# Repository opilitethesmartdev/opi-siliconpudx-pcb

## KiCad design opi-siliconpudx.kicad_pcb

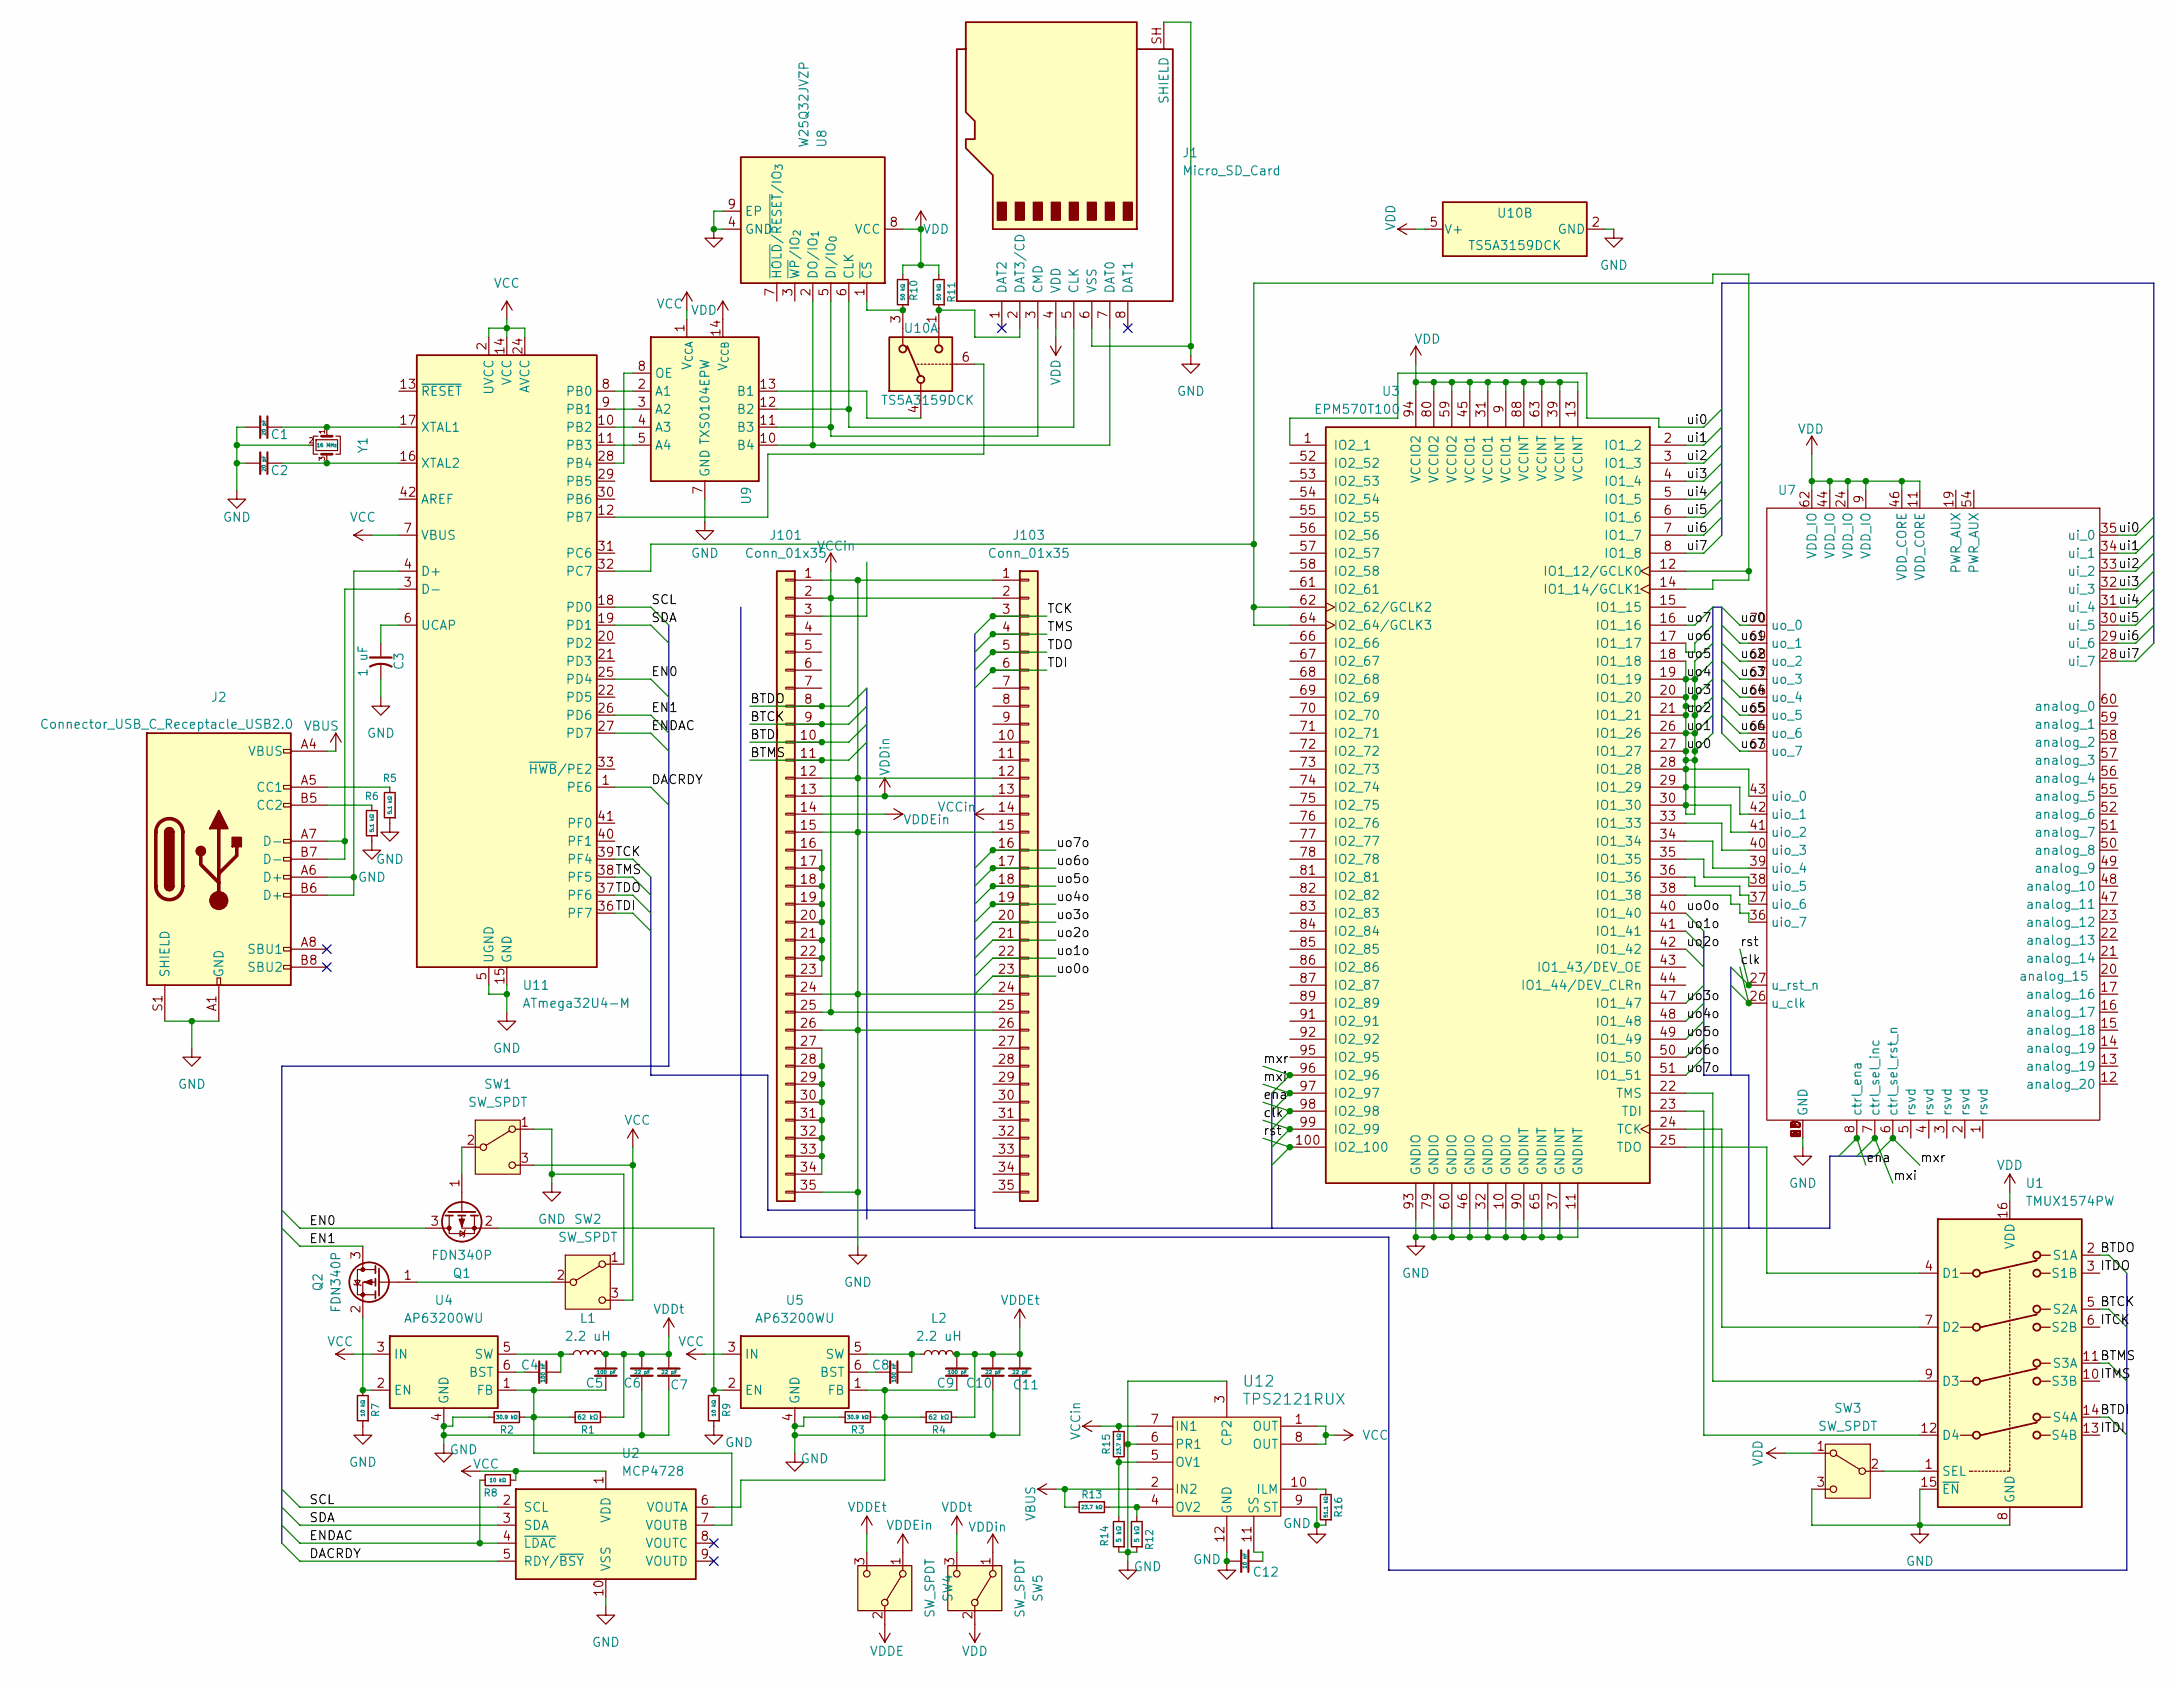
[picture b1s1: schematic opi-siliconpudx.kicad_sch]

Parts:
C1, C2: 20 pF; C_01005_0402Metric
C3: 1 uF; C_0201_0603Metric
C4, C8: 100 nF; C_01005_0402Metric
C5, C9: 100 pF; C_01005_0402Metric
C6, C7, C10, C11: 22 pF; C_01005_0402Metric
C12: 10 nF; C_01005_0402Metric
J1: Micro_SD_Card; microSD_HC_Molex_47219-2001
J2: Connector_USB_C_Receptacle_USB2.0; TYPE-C-31-M-14
J101, J103: Conn_01x35; PinHeader_1x35_P2.54mm_Vertical
L1, L2: 2.2 uH; L_Cenker_CKCS201610
Q1, Q2: FDN340P; SOT-23
R1, R4: 62 kΩ; R_01005_0402Metric
R2, R3: 30.9 kΩ; R_01005_0402Metric
R5, R6: 5.1 kΩ; R_01005_0402Metric
R7, R8, R9: 10 kΩ; R_01005_0402Metric
R10, R11: 50 kΩ; R_01005_0402Metric
R12, R14: 5 kΩ; R_01005_0402Metric
R13, R15: 23.7 kΩ; R_01005_0402Metric
R16: 51.1 kΩ; R_01005_0402Metric
SW1, SW2, SW3, SW4, SW5: SW_SPDT; PinHeader_1x03_P2.00mm_Vertical
U1: TMUX1574PW; TSSOP-16_4.4x5mm_P0.65mm
U2: MCP4728; MSOP-10_3x3mm_P0.5mm
U3: EPM570T100; LQFP-100_14x14mm_P0.5mm
U4, U5: AP63200WU; TSOT-23-6
U7: CONN-SMD_70P-P0.40_HCTL_HC-PBB40C-70DP-0.4V-02
U8: W25Q32JVZP; WSON-8-1EP_6x5mm_P1.27mm_EP3.4x4.3mm
U9: TXS0104EPW; TSSOP-14_4.4x5mm_P0.65mm
U10: TS5A3159DCK; SOT-363_SC-70-6
U11: ATmega32U4-M; QFN-44-1EP_7x7mm_P0.5mm_EP5.2x5.2mm
U12: TPS2121RUX; RUX0012A
Y1: 16 MHz; Crystal_SMD_2016-4Pin_2.0x1.6mm

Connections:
/BTCK: J101.9, U1.5 (S2A)
/BTDI: J101.10, U1.14 (S4A)
/BTDO: J101.8, U1.2 (S1A)
/BTMS: J101.11, U1.11 (S3A)
/DACRDY: U2.5 (RDY/~BSY), U11.1 (PE6)
/EN0: Q1.3 (D), U11.25 (PD4)
/EN1: Q2.3 (D), U11.26 (PD6)
/ENDAC: R8.2, U2.4 (~LDAC), U11.27 (PD7)
/ITCK: U1.6 (S2B)
/ITDI: U1.13 (S4B)
/ITDO: U1.3 (S1B)
/ITMS: U1.10 (S3B)
/SCL: U2.2 (SCL), U11.18 (PD0)
/SDA: U2.3 (SDA), U11.19 (PD1)
/TCK: J103.3, U11.39 (PF4)
/TDI: J103.6, U11.36 (PF7)
/TDO: J103.5, U11.37 (PF6)
/TMS: J103.4, U11.38 (PF5)
/clk: U3.99 (IO2_99), U7.26 (u_clk)
/ena: U3.98 (IO2_98), U7.8 (ctrl_ena)
/mxi: U3.97 (IO2_97), U7.7 (ctrl_sel_inc)
/mxr: U3.96 (IO2_96), U7.6 (ctrl_sel_rst_n)
/rst: U3.100 (IO2_100), U7.27 (u_rst_n)
/ui0: U3.1 (IO2_1), U7.35 (ui_0)
/ui1: U3.2 (IO1_2), U7.34 (ui_1)
/ui2: U3.3 (IO1_3), U7.33 (ui_2)
/ui3: U3.4 (IO1_4), U7.32 (ui_3)
/ui4: U3.5 (IO1_5), U7.31 (ui_4)
/ui5: U3.6 (IO1_6), U7.30 (ui_5)
/ui6: U3.7 (IO1_7), U7.29 (ui_6)
/ui7: U3.8 (IO1_8), U7.28 (ui_7)
/uo0: U3.18 (IO1_18), U3.19 (IO1_19), U3.20 (IO1_20), U3.21 (IO1_21), U3.26 (IO1_26), U3.27 (IO1_27), U3.28 (IO1_28), U3.29 (IO1_29), U3.30 (IO1_30), U7.41 (uio_2), U7.42 (uio_1), U7.43 (uio_0), U7.65 (uo_5), U7.66 (uo_4), U7.67 (uo_3), U7.68 (uo_2), U7.69 (uo_1), U7.70 (uo_0)
/uo0o: J103.23, U3.40 (IO1_40)
/uo1o: J103.22, U3.41 (IO1_41)
/uo2o: J103.21, U3.42 (IO1_42)
/uo3o: J103.20, U3.47 (IO1_47)
/uo4o: J103.19, U3.48 (IO1_48)
/uo5o: J103.18, U3.49 (IO1_49)
/uo6: U3.17 (IO1_17), U7.64 (uo_6)
/uo6o: J103.17, U3.50 (IO1_50)
/uo7: U3.16 (IO1_16), U7.63 (uo_7)
/uo7o: J103.16, U3.51 (IO1_51)
GND: C1.1, C2.1, C3.2, C6.1, C7.1, C10.1, C11.1, C12.2, J1.6 (VSS), J1.SH (SHIELD), J2.A1 (GND), J2.A12 (GND), J2.B1 (GND), J2.B12 (GND), J2.S1 (SHIELD), J101.1, J101.12, J101.15, J101.24, J101.26, J101.35, J103.1, J103.12, J103.15, J103.24, J103.26, R2.1, R3.1, R5.1, R6.1, R7.1, R9.1, R12.1, R14.1, R16.1, SW1.1 (A), SW2.1 (A), SW3.3 (C), U1.8 (GND), U1.15 (~EN), U2.10 (VSS), U3.10 (GNDIO), U3.11 (GNDINT), U3.32 (GNDIO), U3.37 (GNDINT), U3.46 (GNDIO), U3.60 (GNDIO), U3.65 (GNDINT), U3.79 (GNDIO), U3.90 (GNDINT), U3.93 (GNDIO), U4.4 (GND), U5.4 (GND), U7.10 (GND), U7.18 (GND), U7.25 (GND), U7.45 (GND), U7.53 (GND), U7.61 (GND), U7.MP (GND), U8.4 (GND), U8.9 (EP), U9.7 (GND), U10.2 (GND), U11.5 (UGND), U11.15 (GND), U11.23 (GND), U11.35 (GND), U11.43 (GND), U11.45 (GND), U12.3 (CP2), U12.6 (PR1), U12.9 (ST), U12.12 (GND), Y1.2 (G), Y1.4 (G)
unnamed: J1.5 (CLK), U8.6 (CLK), U9.12 (B2)
unnamed: J1.3 (CMD), U8.5 (DI/IO_{0}), U9.11 (B3)
unnamed: J1.7 (DAT0), U8.2 (DO/IO_{1}), U9.10 (B4)
unnamed: J1.2 (DAT3/CD), R11.1, U10.1
unnamed: J2.A5 (CC1), R5.2
unnamed: J2.B5 (CC2), R6.2
unnamed: J101.16, J101.17, J101.18, J101.19, J101.20, J101.21, J101.22, J101.23
unnamed: J101.27, J101.28, J101.29, J101.30, J101.31, J101.32, J101.33, J101.34
unnamed: Q1.1 (G), SW1.2 (B)
unnamed: Q1.2 (S), R9.2, U5.2 (EN)
unnamed: Q2.1 (G), SW2.2 (B)
unnamed: Q2.2 (S), R7.2, U4.2 (EN)
unnamed: SW3.2 (B), U1.1 (SEL)
unnamed: U1.4 (D1), U3.25 (TDO)
unnamed: U1.7 (D2), U3.24 (TCK)
unnamed: U1.9 (D3), U3.22 (TMS)
unnamed: U1.12 (D4), U3.23 (TDI)
unnamed: C9.1, R3.2, R4.1, U2.6 (VOUTA), U5.1 (FB)
unnamed: C5.1, R1.1, R2.2, U2.7 (VOUTB), U4.1 (FB)
unnamed: U3.33 (IO1_33), U7.40 (uio_3)
unnamed: U3.34 (IO1_34), U7.39 (uio_4)
unnamed: U3.35 (IO1_35), U7.38 (uio_5)
unnamed: U3.36 (IO1_36), U7.37 (uio_6)
unnamed: U3.38 (IO1_38), U7.36 (uio_7)
unnamed: C4.1, U4.6 (BST)
unnamed: C4.2, L1.1, U4.5 (SW)
unnamed: C8.1, U5.6 (BST)
unnamed: C8.2, L2.1, U5.5 (SW)
unnamed: R10.1, U8.1 (~CS), U10.3
unnamed: U9.13 (B1), U10.4
unnamed: J2.A6 (D+), J2.B6 (D+), U11.4 (D+)
unnamed: J2.A7 (D-), J2.B7 (D-), U11.3 (D-)
unnamed: U9.2 (A1), U11.8 (PB0)
unnamed: U9.3 (A2), U11.9 (PB1)
unnamed: U9.4 (A3), U11.10 (PB2)
unnamed: U9.5 (A4), U11.11 (PB3)
unnamed: U9.8 (OE), U11.28 (PB4)
unnamed: U10.6, U11.12 (PB7)
unnamed: U3.12 (IO1_12/GCLK0), U3.14 (IO1_14/GCLK1), U3.62 (IO2_62/GCLK2), U3.64 (IO2_64/GCLK3), U11.32 (PC7)
unnamed: C3.1, U11.6 (UCAP)
unnamed: C1.2, U11.17 (XTAL1), Y1.1
unnamed: C2.2, U11.16 (XTAL2), Y1.3
unnamed: R16.2, U12.10 (ILM)
unnamed: R14.2, R15.2, U12.5 (OV1)
unnamed: R12.2, R13.1, U12.4 (OV2)
unnamed: C12.1, U12.11 (SS)
VBUS: J2.A4 (VBUS), J2.A9 (VBUS), J2.B4 (VBUS), J2.B9 (VBUS), R13.2, U12.2 (IN2)
VCC: R8.1, SW1.3 (C), SW2.3 (C), U2.1 (VDD), U4.3 (IN), U5.3 (IN), U9.1 (V_{CCA}), U11.2 (UVCC), U11.7 (VBUS), U11.14 (VCC), U11.24 (AVCC), U11.34 (VCC), U11.44 (AVCC), U12.1 (OUT), U12.8 (OUT)
VCCin: J101.2, J101.25, J103.2, J103.14, J103.25, R15.1, U12.7 (IN1)
VDD: J1.4 (VDD), R10.2, R11.2, SW3.1 (A), SW5.2 (B), U1.16 (VDD), U3.9 (VCCIO1), U3.13 (VCCINT), U3.31 (VCCIO1), U3.39 (VCCINT), U3.45 (VCCIO1), U3.59 (VCCIO2), U3.63 (VCCINT), U3.80 (VCCIO2), U3.88 (VCCINT), U3.94 (VCCIO2), U7.9 (VDD_IO), U7.11 (VDD_CORE), U7.24 (VDD_IO), U7.44 (VDD_IO), U7.46 (VDD_CORE), U7.62 (VDD_IO), U8.8 (VCC), U9.14 (V_{CCB}), U10.5 (V+)
VDDE: SW4.2 (B)
VDDEin: J101.14, SW4.1 (A)
VDDEt: C9.2, C10.2, C11.2, L2.2, R4.2, SW4.3 (C)
VDDin: J101.13, J103.13, SW5.1 (A)
VDDt: C5.2, C6.2, C7.2, L1.2, R1.2, SW5.3 (C)

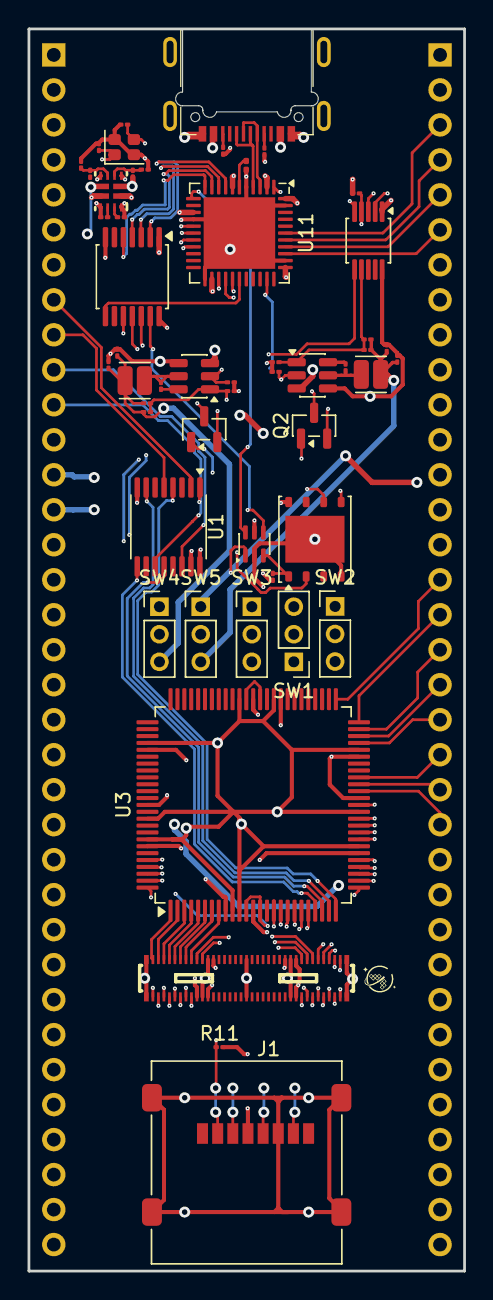
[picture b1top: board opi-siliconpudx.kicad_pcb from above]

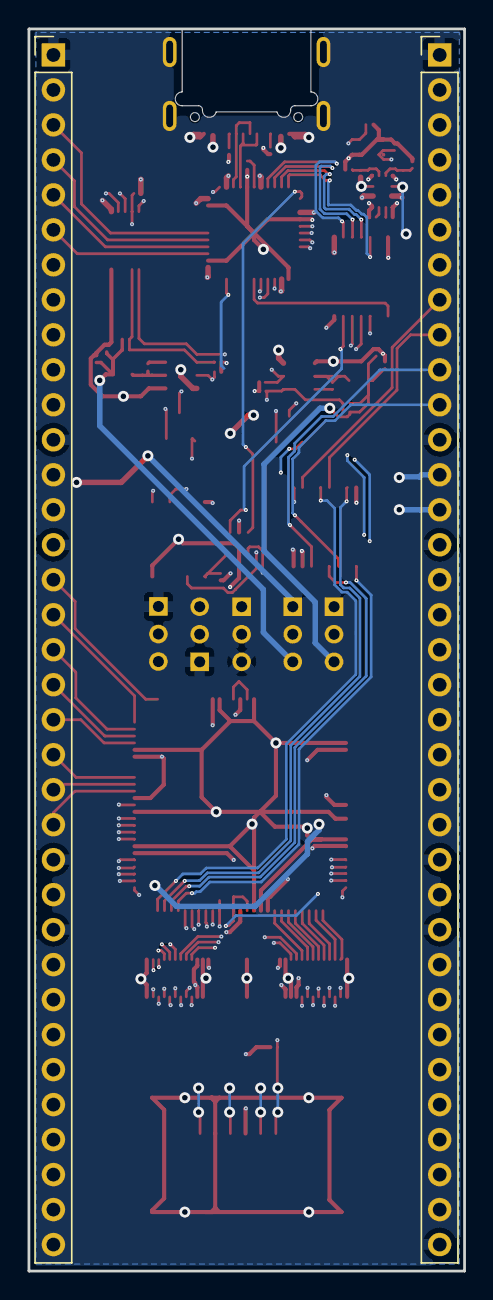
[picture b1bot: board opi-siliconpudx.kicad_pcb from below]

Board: 4 copper layers, 31.6 x 90.2 mm, 53 parts (2 on the bottom side), 93 nets.
